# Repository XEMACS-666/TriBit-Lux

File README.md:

<h1 align="center">☀️ TriBit Lux</h1>

<p align="center"><strong>One light. Eight levels. Three bits.</strong><br>A light-sensing experiment, told through simulations, jumper wires and PCB designs.</p>

<p align="center">
  <strong>3-bit flash ADC concept</strong> &nbsp; · &nbsp;
  <strong>LDR input</strong> &nbsp; · &nbsp;
  <strong>0–7 display</strong> &nbsp; · &nbsp;
  <strong>KiCad + EasyEDA</strong>
</p>

<p align="center">
  
  <br><sub>V2.1 · Compact hybrid design · 5 V input / 2.5 V reference · Not yet fabricated</sub>
</p>

<p align="center">
  <a href="#v21">Latest design · V2.1</a> &nbsp; / &nbsp;
  <a href="Version_2.1/README.md">V2.1 design files</a> &nbsp; / &nbsp;
  <a href="#journey">Version history</a> &nbsp; / &nbsp;
  <a href="#explore">Interactive explorer</a> &nbsp; / &nbsp;
  <a href="#roadmap">What's next</a>
</p>

**TriBit Lux** converts an LDR's output voltage into one of eight brightness levels and shows the result on a seven-segment display. It began in TinkerCAD, moved onto breadboards, and gradually transferred the encoding and display work from an Arduino to dedicated logic ICs.

This repository presents the latest design first, followed by its earlier versions through the material saved along the way: simulations, sketches, lab photographs, schematics, interactive demonstrations and PCB exports. The breadboard wiring is part of the story—getting it into a compact board was a project in itself.

> **Where the project stands:** [V2.1](Version_2.1/README.md) is now an 80 × 41 mm hybrid THT + SMT design with seven cumulative LEDs, a 2.5 V reference, four mounting holes and a back-side repository QR. The 30 October check reports no PCB errors, unconnected items or schematic-parity issues; 57 existing warnings remain. V2.0 stays as the unfabricated THT milestone, and V2.2 will document the fabricated result.

---

## 🧭 Version history · newest first

| Version | Milestone | What changed |
|---|---|---|
| [**V2.1**](#v21) | **Current hybrid design** | Compact THT + SMT board, cumulative LEDs, 2.5 V reference and mounting holes. |
| [V2.0](#v20) | Through-hole PCB | The breadboard connections become an unfabricated KiCad design. |
| [V1.3](#v13) | LCD monitoring | An LCD adds a view of the sensor voltage. |
| [V1.2](#v12) | Hardware display decoding | The 74LS48 drives the display; the Nano monitors the encoder bits. |
| [V1.1](#v11) | Hardware priority encoding | The 74F148 takes over encoding; the Nano still drives the display. |
| [V1.0](#v10) | First breadboard | The LDR and comparator front end move into a physical build. |
| [V0.1](#v01) | LDR simulation | Light becomes the input to the simulated comparator circuit. |
| [V0.0](#v00) | Potentiometer simulation | The original voltage-to-level experiment. |

V2.2 is the planned fabricated result; see [what’s next](#roadmap).

---

## ✨ V2.1 · Smaller board, clearer feedback

**80 × 41 mm · Hybrid THT + SMT · Seven cumulative LEDs · 2.5 V reference**

The light-sensing circuit now fits on a compact rectangle with a regular resistor/LED column, two comparator banks, dedicated encoder and decoder ICs, and a buffer for the threshold LEDs. Four mounting holes form a symmetric 73 × 34 mm pattern, with their centres 3.5 mm from adjacent straight board edges. The underside carries a threshold guide and a repository QR code.

| Front · Read the layout | Back · Follow the levels |
|:---:|:---:|
|  |  |

JLCPCB is planned to assemble **39 SMT parts per board**; XEMACS will solder the **17 through-hole parts**. The three-pin header provides 5 V input, ground and the analog sensor voltage for measurement. The nominal thresholds are spaced by 0.3125 V; the displayed level is not calibrated lux.

These are XEMACS’s existing CAD exports. They precede the 30 October silkscreen alignment; updated high-resolution renders will be supplied by XEMACS.

### Schematic · V2.1 hybrid circuit

*Click the schematic to view XEMACS’s full-resolution export.*

The schematic brings together the regulated **2.5 V sensor/reference rail**, the **LM339 → 74LS148 → 74LS48** display path, and the **74HCT244-driven threshold LEDs**. J1 provides 5 V input, ground and the analog sensor-voltage output.

[Editable KiCad schematic](Version_2.1/TriBitLux_V2_1/TriBitLux_V2_1.kicad_sch) · [Current netlist](Version_2.1/schematic/TriBitLux_V2_1.net) · [Full-resolution schematic image](Version_2.1/assets/Schematic.png)

**Design checkpoint · 30 October 2026:** PCB DRC reports zero errors, zero unconnected items and zero schematic-parity issues, with 57 existing warnings. Schematic ERC reports zero violations. The board remains unfabricated, and the next manufacturing export needs a fresh supplier DFM check. The older explorer’s V2.1 concept predates this 2.5 V implementation.

[Full V2.1 gallery and files](Version_2.1/README.md) · [KiCad project](Version_2.1/TriBitLux_V2_1/TriBitLux_V2_1.kicad_pro) · [Schematic](Version_2.1/TriBitLux_V2_1/TriBitLux_V2_1.kicad_sch) · [SMT BOM](Version_2.1/bom/TriBitLux_V2_1_JLCPCB_SMT.csv) · [SMT placement](Version_2.1/cpl/TriBitLux_V2_1_JLCPCB_SMT_CPL.csv) · [Layout review](Version_2.1/review/README.md)

---

## 🟢 V2.0 · From jumper wires to copper traces

**KiCad design · Through-hole components · Unfabricated**

V2.0 brings the circuit into KiCad as an editable schematic and PCB. The design includes a 20 mm LDR, a potentiometer for adjusting the response, local decoupling capacitors and a regulated 3.3 V rail for the sensor divider and reference ladder.

| Sensor | Adjustment | Power and references | Construction |
|---|---|---|---|
| 20 mm LDR | Potentiometer in the divider | 5 V logic; 3.3 V sensor and ladder | Through-hole board |

### The board, four ways

<p align="center">
  
  <br><sub>Component-populated CAD preview. The LDR and potentiometer have no visible models in this render; both remain in the design and BOM.</sub>
</p>

| Read the board | Follow the routing |
|:---:|:---:|
|  |  |
| **Top · Silkscreen and placement** | **Layout · Copper and connections** |

<p align="center">
  
  <br><sub>Underside of the saved PCB design. All board images here are CAD views, not fabricated hardware.</sub>
</p>

### Read the silkscreen

| Printed label | Circuit reference | Purpose |
|---|---|---|
| **LM339-A** | U1 | Upper threshold comparators plus the ground-reference comparator |
| **LM339-B** | U2 | Lower threshold comparators, from 0.4125 V to 1.650 V |
| **74LS148 – ENCODER** | U3 | Converts active comparator inputs into three bits |
| **74LS48 – DECODER** | U4 | Drives the seven-segment display |
| **D198K** | U5 | Displays the selected level |
| **LDR / SENSITIVITY** | R9 / RV1 | Light input and divider adjustment |
| **3V3 / 5V IN** | U6 / J2 | Regulated reference supply and external power input |
| **0 V → 2.8875 V** | R8 → R1, left to right | Nominal lower-voltage end of each 10 kΩ ladder resistor |

The ladder labels identify nominal nodes, not voltage drops across the resistors. Each resistor spans 0.4125 V ideally; the far end of R1 reaches 3.3 V. Circuit references remain in the editable design and parts lists.

The current revision includes revised capacitor footprints, a 15.5 mm lead pitch for the 20 mm LDR, a repository QR graphic, and XEMACS attribution. The custom capacitor and QR footprints are included in the project library.

### Schematic · current source export

*Click for the PDF, or open the [scalable SVG](Version_2.0/assets/TriBitLux_V2_0.svg). The [older PNG export](Version_2.0/assets/TriBit_Lux_V2_0_Schematics.png) is retained as an earlier snapshot.*

### Design checkpoint · 19 October 2026

| Check | Result |
|---|---|
| KiCad PCB DRC | 0 reported violations; 0 unconnected items |
| Schematic ↔ PCB parity | 0 reported mismatches |
| Schematic ERC | 0 reported violations |
| BOM / placement coverage | 41 components; refreshed JLCPCB-format exports |
| Fabrication / assembly | Not performed; supplier selection and final export review remain open |

These results use the project's configured rules. Some footprint/courtyard checks are disabled; this is not a manufacturer DFM approval. See the [review and remaining work](Version_2.0/review/README.md) for the exact limits and open items.

### Inside the circuit

```text
                         3.3 V reference ladder
                                  │
Light → LDR + potentiometer → LM339 comparators → Priority encoder → 74LS48 → 0–7
         sensor voltage          parallel decisions     three bits       display
```

| Stage | What happens |
|---|---|
| **1 · Sense** | Light lowers the LDR resistance. In the current divider arrangement, the sensor voltage rises as the LDR resistance falls. |
| **2 · Compare** | Seven nonzero ladder references divide the nominal 0–3.3 V range into eight bands, spaced by 0.4125 V. |
| **3 · Encode** | The highest-priority active LOW input determines the output. I7 through I1 receive thresholds from 0.4125 V up to 2.8875 V; I0 uses the eighth comparator with its ground reference on the opposite input. |
| **4 · Display** | Encoder outputs S0, S1 and S2 connect to decoder inputs A, B and C. D is grounded, keeping the displayed range at 0–7. |

The comparator and logic ICs use **5 V**. The sensor divider and reference ladder use the regulated **3.3 V** rail. Earlier breadboards used a **74F148**; the current V2.0 CAD source specifies a **74LS148**.

> **About the number on the display:** it is a relative brightness level, not calibrated lux. The LDR, potentiometer setting and component tolerances influence the physical transition points.

### Open the V2.0 design

| Resource | Direct links |
|---|---|
| **KiCad source** | [Project](Version_2.0/TriBitLux_V2_0/TriBitLux_V2_0.kicad_pro) · [Schematic](Version_2.0/TriBitLux_V2_0/TriBitLux_V2_0.kicad_sch) · [PCB](Version_2.0/TriBitLux_V2_0/TriBitLux_V2_0.kicad_pcb) |
| **Schematic exports** | [PDF](Version_2.0/schematic/TriBit_Lux_V2_0_Schematics.pdf) · [Current SVG](Version_2.0/assets/TriBitLux_V2_0.svg) · [Earlier PNG](Version_2.0/assets/TriBit_Lux_V2_0_Schematics.png) · [Netlist](Version_2.0/schematic/TriBitLux_V2_0.net) |
| **Parts lists** | [BOM](Version_2.0/bom/TriBitLux_V2_0_BOM.csv) · [JLCPCB BOM](Version_2.0/bom/TriBitLux_V2_0-BOM-JLCPCB.csv) |
| **Placement exports** | [Top](Version_2.0/cpl/TriBitLux_V2_0-top-pos.csv) · [Bottom](Version_2.0/cpl/TriBitLux_V2_0-bottom-pos.csv) · [JLCPCB top](Version_2.0/cpl/TriBitLux_V2_0-top-pos-JLCPCB.csv) |
| **Manufacturing snapshot · JLCONE pass reported** | [Gerber ZIP](Version_2.0/Gerber/gerber.zip) |
| **Custom footprints** | [Project library](Version_2.0/TriBitLux_V2_0/TriBitLux.pretty/) · [Library table](Version_2.0/TriBitLux_V2_0/fp-lib-table) |
| **Review** | [Checks and remaining work](Version_2.0/review/README.md) |
| **Interactive documentation** | [Live explorer](https://xemacs-666.github.io/TriBit-Lux/Version_2.0/assets/tribit-lux-explorer.html) · [Standalone HTML](Version_2.0/assets/tribit-lux-explorer.html) · [GIF preview](Version_2.0/assets/tribit-lux-preview.gif) |

Open `TriBitLux_V2_0.kicad_pro` in KiCad to work with the schematic and PCB together. The editable files are the design sources. The JLCPCB CSVs now reflect the current component list and saved placement export. Blank supplier codes require part selection; retained codes are historical selections that still need verification. XEMACS reports that the KiCad export passed all JLCONE checks. Preserve the exact checked archive; regenerate it after any further manufacturing-layer changes. A later PCB save timestamp alone does not establish that the archive is stale.

---

## 📟 V1.3 · A window into the sensor voltage

**Physical prototype · 16×2 I²C LCD · Parallel monitoring**

The Nano gained another role: driving an LCD to make the working flow easier to follow. The hardware seven-segment path remained in place, while the Nano supplied power and sampled the LDR voltage through its own ADC.

| LCD-equipped breadboard | Another view of the build |
|:---:|:---:|
|  |  |

### Explore the LCD demonstration

| 5 V demonstration | 3.3 V demonstration |
|:---:|:---:|
| [**Open interactive 5 V view →**](https://xemacs-666.github.io/TriBit-Lux/Version_1.3/assets/TriBitLux_V1_3_%285V%29.html) | [**Open interactive 3.3 V view →**](https://xemacs-666.github.io/TriBit-Lux/Version_1.3/assets/TriBitLux_V1_3_%283.3V%29.html) |
| [HTML source](Version_1.3/assets/TriBitLux_V1_3_%285V%29.html) | [HTML source](Version_1.3/assets/TriBitLux_V1_3_%283.3V%29.html) |

The LCD firmware calculates its own level from the analog voltage; it **does not read the encoder bits**. That makes the LCD useful for observing the input, while the hardware display follows the comparator and encoder chain. These saved demonstrations belong to the V1.3 archive; the main explorer shows the updated V2.0 logic model.

**Open this version:** [LCD sketch](Version_1.3/firmware/TriBitLux_V1_3/TriBitLux_V1_3.ino) · [Original assets](Version_1.3/assets/)

---

## 🔢 V1.2 · Hardware takes over the display

**Physical prototype · 74LS48 decoder · Serial monitoring**

Adding the 74LS48 completed the dedicated hardware display path: comparator bank → encoder → decoder → seven-segment display. The Nano supplied 5 V and received the three encoder bits so the serial console could show them for assurance.

### The wiring, up close

| Overhead wiring view | Sensor and jumper connections |
|:---:|:---:|
|  |  |

<p align="center">
  
  <br><sub>The powered build. The photographed display is driven by the 74LS48.</sub>
</p>

| Additional powered view | A second captured state |
|:---:|:---:|
|  |  |

*The last two previews link to the original HEIC photographs. Large photographs throughout this page use smaller preview copies; click them for the originals.*

**Open this version:** [Serial-monitor sketch](Version_1.2/firmware/TriBitLux_V1_2_LIC/TriBitLux_V1_2_LIC.ino) · [Original photo collection](Version_1.2/assets/)

The saved sketch includes experimental segment-driving code. In the photographed build, the **74LS48 drives the display**, while the Nano observes the encoder output.

---

## 🧠 V1.1 · Giving the encoder its own IC

**Physical prototype · 74F148 priority encoder · EasyEDA design exports**

The 74F148 took over priority encoding from the Nano. The comparator bank now fed a dedicated logic IC, which produced the three output bits. The Nano continued to decode those bits and drive the display. This version also has an EasyEDA schematic and PCB design archive.

### At the workbench

| Schematic beside the build | Full demonstration setup |
|:---:|:---:|
|  |  |
| **Schematic and wiring together** | **Display and reference table** |

| Watching the output | Another angle of the setup |
|:---:|:---:|
|  |  |
| **Hardware output alongside monitoring** | **The complete workbench arrangement** |

### From connections to a board design

| Schematic | Routed PCB layout |
|:---:|:---:|
|  |  |

<p align="center">
  
  <br><sub>EasyEDA design render with the Nano fitted. This image documents the board design.</sub>
</p>

| Top board view · SVG | Bottom board view · SVG |
|:---:|:---:|
|  |  |

**Open this version:** [Schematic PDF](Version_1.1/schematic/Schematic_TriBitLux_V1_1-LIC_2026-10-06.pdf) · [PCB PDF](Version_1.1/pcb/PCB_PCB_TriBitLux_V1_1-LIC_2_2026-10-06.pdf) · [Arduino sketch](Version_1.1/firmware/TriBitLux_V1_1_LIC/TriBitLux_V1_1_LIC.ino) · [BOM](Version_1.1/bom/BOM_TriBitLux_V1_1-LIC_2026-10-06.csv) · [Gerber archive](Version_1.1/gerbers/Gerber_TriBitLux_V1_1-LIC_PCB_TriBitLux_V1_1-LIC_2_2026-10-06.zip)

<details>
<summary><strong>Browse the individual EasyEDA layer PDFs</strong></summary>

| Export | Top | Bottom |
|---|---|---|
| Copper | [Top layer](Version_1.1/pcb/PCB_PCB_TriBitLux_V1_1-LIC_2_2026-10-06/TopLayer.pdf) | [Bottom layer](Version_1.1/pcb/PCB_PCB_TriBitLux_V1_1-LIC_2_2026-10-06/BottomLayer.pdf) |
| Silkscreen | [Top silk](Version_1.1/pcb/PCB_PCB_TriBitLux_V1_1-LIC_2_2026-10-06/TopSilkLayer.pdf) | [Bottom silk](Version_1.1/pcb/PCB_PCB_TriBitLux_V1_1-LIC_2_2026-10-06/BottomSilkLayer.pdf) |
| Solder mask | [Top mask](Version_1.1/pcb/PCB_PCB_TriBitLux_V1_1-LIC_2_2026-10-06/TopSolderMaskLayer.pdf) | [Bottom mask](Version_1.1/pcb/PCB_PCB_TriBitLux_V1_1-LIC_2_2026-10-06/BottomSolderMaskLayer.pdf) |
| Paste mask | [Top paste](Version_1.1/pcb/PCB_PCB_TriBitLux_V1_1-LIC_2_2026-10-06/TopPasteMaskLayer.pdf) | [Bottom paste](Version_1.1/pcb/PCB_PCB_TriBitLux_V1_1-LIC_2_2026-10-06/BottomPasteMaskLayer.pdf) |

[Board outline](Version_1.1/pcb/PCB_PCB_TriBitLux_V1_1-LIC_2_2026-10-06/BoardOutLine.pdf) · [Holes](Version_1.1/pcb/PCB_PCB_TriBitLux_V1_1-LIC_2_2026-10-06/Hole.pdf) · [Multi-layer](Version_1.1/pcb/PCB_PCB_TriBitLux_V1_1-LIC_2_2026-10-06/Multi-Layer.pdf) · [Document layer](Version_1.1/pcb/PCB_PCB_TriBitLux_V1_1-LIC_2_2026-10-06/Document.pdf)

</details>

---

## 🔌 V1.0 · The first breadboard

**Physical prototype · Two LM339s · Arduino Nano**

The LDR and comparator bank moved out of the simulator and onto a breadboard. The Nano read the comparator outputs and drove the seven-segment display. The saved recording captures the early physical build, with the jumper wiring fully on show.

<p align="center">
  
  <br><strong><a href="Version_1.0/assets/TriBitLux_V1_0%202026-10-06%20at%2023.10.18.mp4">▶ Watch the breadboard recording · 24 seconds</a></strong>
</p>

### A closer look at the display pins

*Click the animation to explore the display pin layout.*

**Open this version:** [Recording](Version_1.0/assets/TriBitLux_V1_0%202026-10-06%20at%2023.10.18.mp4) · [Interactive pin guide](https://xemacs-666.github.io/TriBit-Lux/Version_1.0/assets/TriBitLux_V1_0_pin_visualizer.html) · [HTML source](Version_1.0/assets/TriBitLux_V1_0_pin_visualizer.html) · [Visualizer sketch](Version_1.0/firmware/TriBitLux_V1_0_visualizer/TriBitLux_V1_0_visualizer.ino)

The saved visualizer sketch is a debugging aid; it is not the complete original V1.0 display firmware.

---

## 🌤️ V0.1 · Let there be light

**TinkerCAD simulation · LDR input · LM339 comparators**

The potentiometer input was replaced with an LDR, and the comparator section moved to LM339 devices. Now the input responded to light. The Uno still supplied both digital stages: deciding the encoded value and converting it into segment signals.

*The sensor enters the picture. The display logic is still handled by the Uno.*

**Open this version:** [Simulation](https://www.tinkercad.com/things/gNVAR2cQYVG-tribit-lux-v01?sharecode=9jLX_zzwRAG0_mHYH1R4YNfyqPdioSTKhPsh0a257ho) · [Schematic PDF](Version_0.1/schematic/Tribit%20Lux%20V0.1.pdf) · [Arduino sketch](Version_0.1/firmware/tribit_lux_v0_01/tribit_lux_v0_01.ino) · [BOM](Version_0.1/bom/bom.csv)

---

## 🧪 V0.0 · Starting with a knob

**TinkerCAD simulation · Potentiometer input · Arduino Uno**

The first version used a potentiometer to stand in for the sensor voltage. Turning the knob changed the input to the comparator bank, while the Uno performed priority encoding and drove the seven-segment display. This established the basic voltage-to-level idea before adding a light-sensitive input.

*The starting point. Click the circuit image to open its TinkerCAD simulation.*

**Open this version:** [Simulation](https://www.tinkercad.com/things/60Tk7pVbgVW-tribit-lux-v00?sharecode=bsW5T545n6U2o7TxL7Ta_quI-Dl-KoERqczIX1Q8Fq4) · [Schematic PDF](Version_0.0/schematic/Tribit%20Lux%20V0.0.pdf) · [Arduino sketch](Version_0.0/firmware/tribit_lux_v0_00/tribit_lux_v0_00.ino) · [BOM](Version_0.0/bom/bom.csv)

---

## 🎛️ Explore the project

<p align="center">
  
</p>

<p align="center"><strong><a href="https://xemacs-666.github.io/TriBit-Lux/Version_2.0/assets/tribit-lux-explorer.html">Open the interactive TriBit Lux explorer →</a></strong></p>

| Follow the evolution | Trace a signal | Preview the next revision |
|---|---|---|
| Select a version and watch the role of the Arduino change. | Move the voltage slider and follow the comparator outputs, three encoder bits and displayed digit. | Switch to the V2.1 concept to see cumulative threshold lights. |

The preview above is animated; the linked page is interactive. The explorer uses the updated V2.0 reference mapping, including the level-0 band. It models ideal logic, with real-world tolerances, noise and timing left out. [Open the standalone HTML file](Version_2.0/assets/tribit-lux-explorer.html).

---

## 🚧 What's next

| **V2.0 · Preserve** | **V2.1 · Refine** | **V2.2 · Build** |
|---|---|---|
| Keep the full THT design as an unfabricated milestone. | Review the compact 80 × 41 mm hybrid design and refresh its manufacturing exports. | Fabricate and assemble the completed design. |
| Retain its schematic, layout and development record. | Refine threshold lights, silkscreen and assembly details. | Record power-up measurements, light response and the finished assembly. |
| **Current design archive** | Design the acrylic enclosure around the four mounting holes and confirm the on-board QR scans reliably. | Fit the enclosure and document the physical result. |

The planned lights should make each level transition easier to see. The acrylic enclosure should make the circuit easier to display while providing secure mounting. Support components such as decoupling and protection remain electrically important whether their packages are THT or SMT.

## 📂 Finding your way around

```text
TriBit-Lux/
├── README.md                    Illustrated project walkthrough
├── docs/media/                  Photo previews and video poster
├── Version_2.1/
│   ├── README.md                Hybrid board gallery, pinout and status
│   ├── TriBitLux_V2_1/          Editable KiCad project, schematic and PCB
│   ├── assets/                 XEMACS’s board renders and schematic image
│   ├── schematic/              Current netlist
│   ├── bom/                    Full and SMT-only parts lists
│   ├── cpl/                    Native and JLCPCB placement exports
│   └── review/                 Current checks and layout feedback
├── Version_2.0/                 Unfabricated through-hole milestone
├── Version_1.3/                 LCD build and demonstrations
├── Version_1.2/                 Hardware decoder and serial sketch
├── Version_1.1/                 Encoder build and EasyEDA archive
├── Version_1.0/                 First breadboard and pin visualizer
├── Version_0.1/                 LDR simulation
└── Version_0.0/                 Potentiometer simulation
```

Each version folder contains the records that survived that stage. Older versions may not contain a complete build package. The photographs, videos and interactive pages show the development process; the editable design files describe the circuit. KiCad temporary files and backups are excluded through `.gitignore`.

<p align="center"><strong>Built and documented by XEMACS</strong><br>From a simulated input to a board designed around light.<br><br><a href="#explore">Try the explorer</a> · <a href="#v21">Back to the latest design</a> · <a href="https://github.com/XEMACS-666/TriBit-Lux">Repository</a></p>

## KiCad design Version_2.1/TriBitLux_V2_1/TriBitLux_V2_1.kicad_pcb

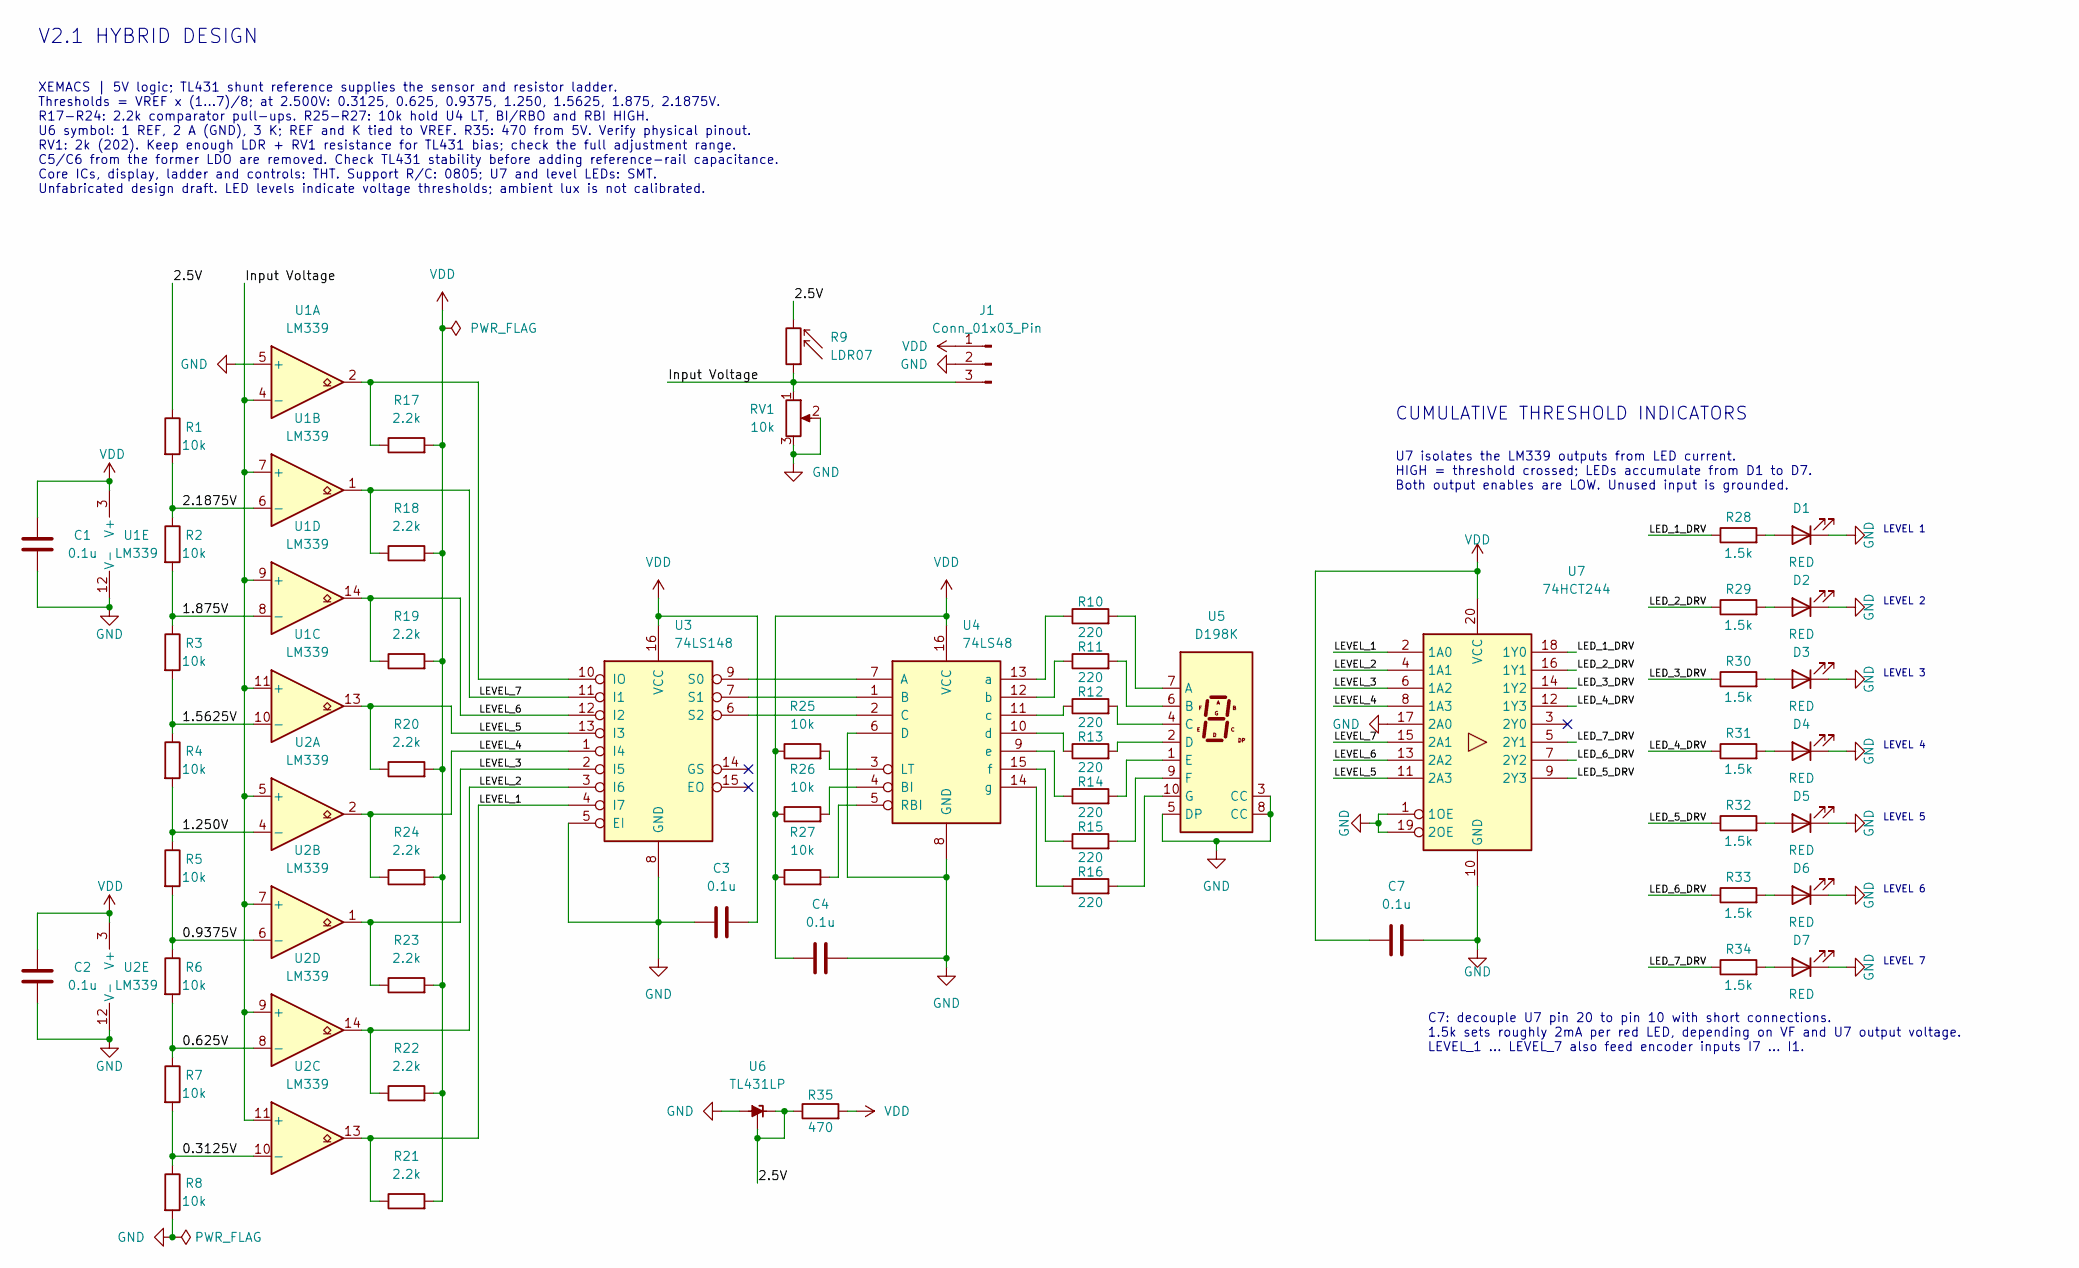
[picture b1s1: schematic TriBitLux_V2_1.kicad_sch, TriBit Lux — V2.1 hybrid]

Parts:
C1, C2, C3, C4, C7: 0.1u; C_0805_2012Metric_Pad1.18x1.45mm_HandSolder
D1, D2, D3, D4, D5, D6, D7: RED; LED_0805_2012Metric_Pad1.15x1.40mm_HandSolder
J1: Conn_01x03_Pin; TerminalBlock_Xinya_XY308-2.54-3P_1x03_P2.54mm_Horizontal
R1, R2, R3, R4, R5, R6, R7, R8: 10k; R_Axial_DIN0207_L6.3mm_D2.5mm_P7.62mm_Horizontal
R9: LDR07; R_LDR_D20mm_P15.5mm_Vertical
R10, R11, R12, R13, R14, R15, R16: 220; R_0805_2012Metric_Pad1.20x1.40mm_HandSolder
R17, R18, R19, R20, R21, R22, R23, R24: 2.2k; R_0805_2012Metric_Pad1.20x1.40mm_HandSolder
R25, R26, R27: 10k; R_0805_2012Metric_Pad1.20x1.40mm_HandSolder
R28, R29, R30, R31, R32, R33, R34: 1.5k; R_0805_2012Metric_Pad1.20x1.40mm_HandSolder
R35: 470; R_0805_2012Metric_Pad1.20x1.40mm_HandSolder
RV1: 10k; Potentiometer_Runtron_RM-065_Vertical
U1, U2: LM339; DIP-14_W7.62mm_Socket
U3: 74LS148; DIP-16_W7.62mm_Socket
U4: 74LS48; DIP-16_W7.62mm_Socket
U5: D198K; 7SegmentLED_LTS6760_LTS6780
U6: TL431LP; TL431_TO92_Body4.1x3.1mm_P1.27mm
U7: 74HCT244; SOIC-20W_7.5x12.8mm_P1.27mm

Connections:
/0.625V: R6.2, R7.1, U2.8 (-)
/0.3125V: R7.2, R8.1, U2.10 (-)
/0.9375V: R5.2, R6.1, U2.6 (-)
/1.250V: R4.2, R5.1, U2.4 (-)
/1.875V: R2.2, R3.1, U1.8 (-)
/1.5625V: R3.2, R4.1, U1.10 (-)
/2.5V: R1.1, R9.2, R35.1, U6.1 (REF), U6.3 (K)
/2.1875V: R1.2, R2.1, U1.6 (-)
/Input Voltage: J1.3, R9.1, RV1.1, U1.4 (-), U1.7 (+), U1.9 (+), U1.11 (+), U2.5 (+), U2.7 (+), U2.9 (+), U2.11 (+)
/LED_1_DRV: R28.1, U7.18 (1Y0)
/LED_2_DRV: R29.1, U7.16 (1Y1)
/LED_3_DRV: R30.1, U7.14 (1Y2)
/LED_4_DRV: R31.1, U7.12 (1Y3)
/LED_5_DRV: R32.1, U7.9 (2Y3)
/LED_6_DRV: R33.1, U7.7 (2Y2)
/LED_7_DRV: R34.1, U7.5 (2Y1)
/LEVEL_1: R21.1, U2.13, U3.4 (I7), U7.2 (1A0)
/LEVEL_2: R22.1, U2.14, U3.3 (I6), U7.4 (1A1)
/LEVEL_3: R23.1, U2.1, U3.2 (I5), U7.6 (1A2)
/LEVEL_4: R24.1, U2.2, U3.1 (I4), U7.8 (1A3)
/LEVEL_5: R20.1, U1.13, U3.13 (I3), U7.11 (2A3)
/LEVEL_6: R19.1, U1.14, U3.12 (I2), U7.13 (2A2)
/LEVEL_7: R18.1, U1.1, U3.11 (I1), U7.15 (2A1)
GND: C1.2, C2.2, C3.2, C4.1, C7.2, D1.1 (K), D2.1 (K), D3.1 (K), D4.1 (K), D5.1 (K), D6.1 (K), D7.1 (K), J1.2, R8.2, RV1.2, RV1.3, U1.5 (+), U1.12 (V-), U2.12 (V-), U3.5 (EI), U3.8 (GND), U4.6 (D), U4.8 (GND), U5.3 (CC), U5.5 (DP), U5.8 (CC), U6.2 (A), U7.1 (1OE), U7.10 (GND), U7.17 (2A0), U7.19 (2OE)
unnamed: D1.2 (A), R28.2
unnamed: D2.2 (A), R29.2
unnamed: D3.2 (A), R30.2
unnamed: D4.2 (A), R31.2
unnamed: D5.2 (A), R32.2
unnamed: D6.2 (A), R33.2
unnamed: D7.2 (A), R34.2
unnamed: R17.1, U1.2, U3.10 (IO)
unnamed: U3.9 (S0), U4.7 (A)
unnamed: U3.7 (S1), U4.1 (B)
unnamed: U3.6 (S2), U4.2 (C)
unnamed: R26.2, U4.4 (BI)
unnamed: R25.2, U4.3 (LT)
unnamed: R27.2, U4.5 (RBI)
unnamed: R10.1, U4.13 (a)
unnamed: R11.1, U4.12 (b)
unnamed: R12.1, U4.11 (c)
unnamed: R13.1, U4.10 (d)
unnamed: R14.1, U4.9 (e)
unnamed: R15.1, U4.15 (f)
unnamed: R16.1, U4.14 (g)
unnamed: R10.2, U5.7 (A)
unnamed: R11.2, U5.6 (B)
unnamed: R12.2, U5.4 (C)
unnamed: R13.2, U5.2 (D)
unnamed: R14.2, U5.1 (E)
unnamed: R15.2, U5.9 (F)
unnamed: R16.2, U5.10 (G)
VDD: C1.1, C2.1, C3.1, C4.2, C7.1, J1.1, R17.2, R18.2, R19.2, R20.2, R21.2, R22.2, R23.2, R24.2, R25.1, R26.1, R27.1, R35.2, U1.3 (V+), U2.3 (V+), U3.16 (VCC), U4.16 (VCC), U7.20 (VCC)

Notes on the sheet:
CUMULATIVE THRESHOLD INDICATORS
U7 isolates the LM339 outputs from LED current. HIGH = threshold crossed; LEDs accumulate from D1 to D7. Both output enables are LOW. Unused input is grounded.
LEVEL 4
LEVEL 3
XEMACS | 5V logic; TL431 shunt reference supplies the sensor and resistor ladder. Thresholds = VREF x (1...7)/8; at 2.500V: 0.3125, 0.625, 0.9375, 1.250, 1.5625, 1.875, 2.1875V. R17-R24: 2.2k comparator pull-ups. R25-R27: 10k hold U4 LT, BI/RBO and RBI HIGH. U6 symbol: 1 REF, 2 A (GND), 3 K; REF an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
LEVEL 7
LEVEL 2
LEVEL 1
LEVEL 5
V2.1 HYBRID DESIGN
C7: decouple U7 pin 20 to pin 10 with short connections. 1.5k sets roughly 2mA per red LED, depending on VF and U7 output voltage. LEVEL_1 ... LEVEL_7 also feed encoder inputs I7 ... I1.
LEVEL 6

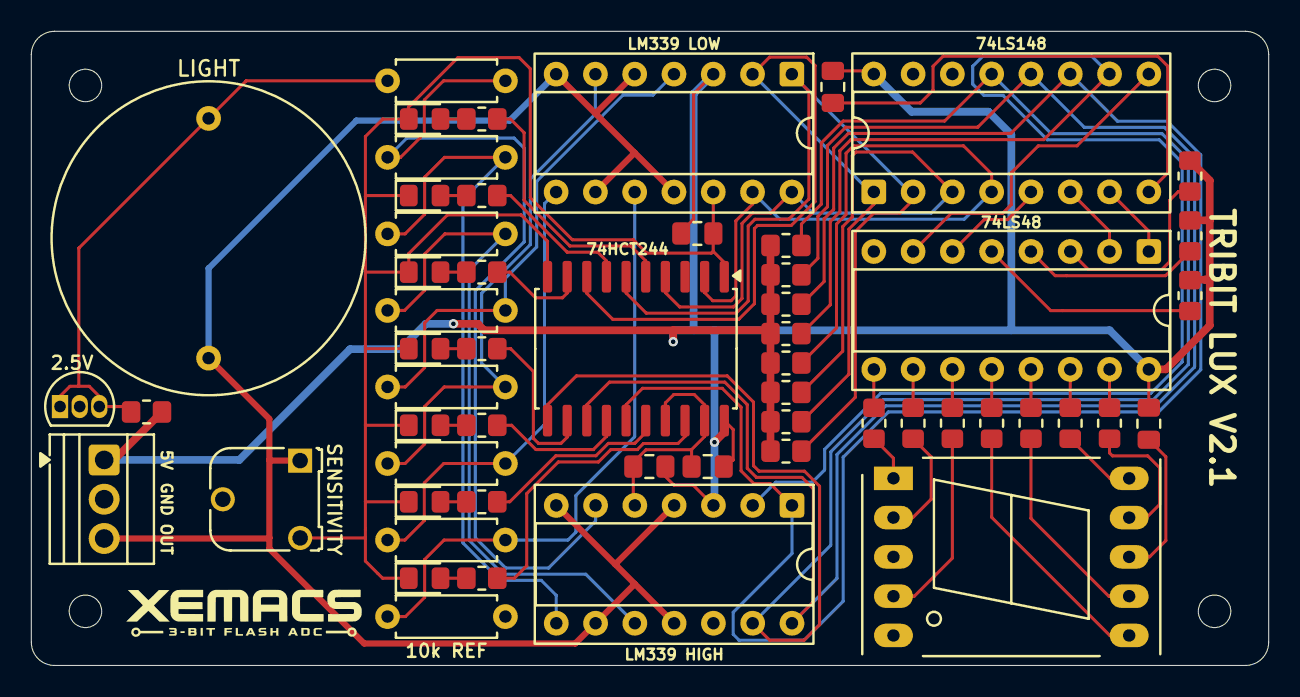
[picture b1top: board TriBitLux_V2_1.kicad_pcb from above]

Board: 2 copper layers, 80.0 x 41.0 mm, 60 parts (0 on the bottom side), 53 nets.

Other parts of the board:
H1, H2, H3, H4: MountingHole_2.1mm
